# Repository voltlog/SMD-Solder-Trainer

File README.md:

# SMD-Solder-Trainer
This repository holds source file for the Voltlog SMD Solder Trainer

I designed this PCB to help people test their SMD soldering skills. It contains passives from 01005 up to 1206 as well as several chip packages. If you solder all resistors in a row and the LED correctly, by applying 5V to the bottom header you should get a light on the LED. Although not entirely necessary, if you order this board with ENIG gold finish it should help with soldering the smallest pads.

Here is a list of tools & supplies that I used in this project:
* 2x3W Gooseneck Microscope Light http://voltlog.com/y/2gxc9
* Trinocular Microscope http://voltlog.com/y/tcmpe
* Hayear 1080P Camera http://voltlog.com/y/uh7pv
* 10” 2K HDMI Monitor http://voltlog.com/y/nq7rv
* KSGER T12 Soldering Station http://voltlog.com/y/2tzg7
* PCB files Kicad/Gerber (in this repository)

More info about this project in [Voltlog #328](https://youtu.be/IcV3Eh1Z-N4).

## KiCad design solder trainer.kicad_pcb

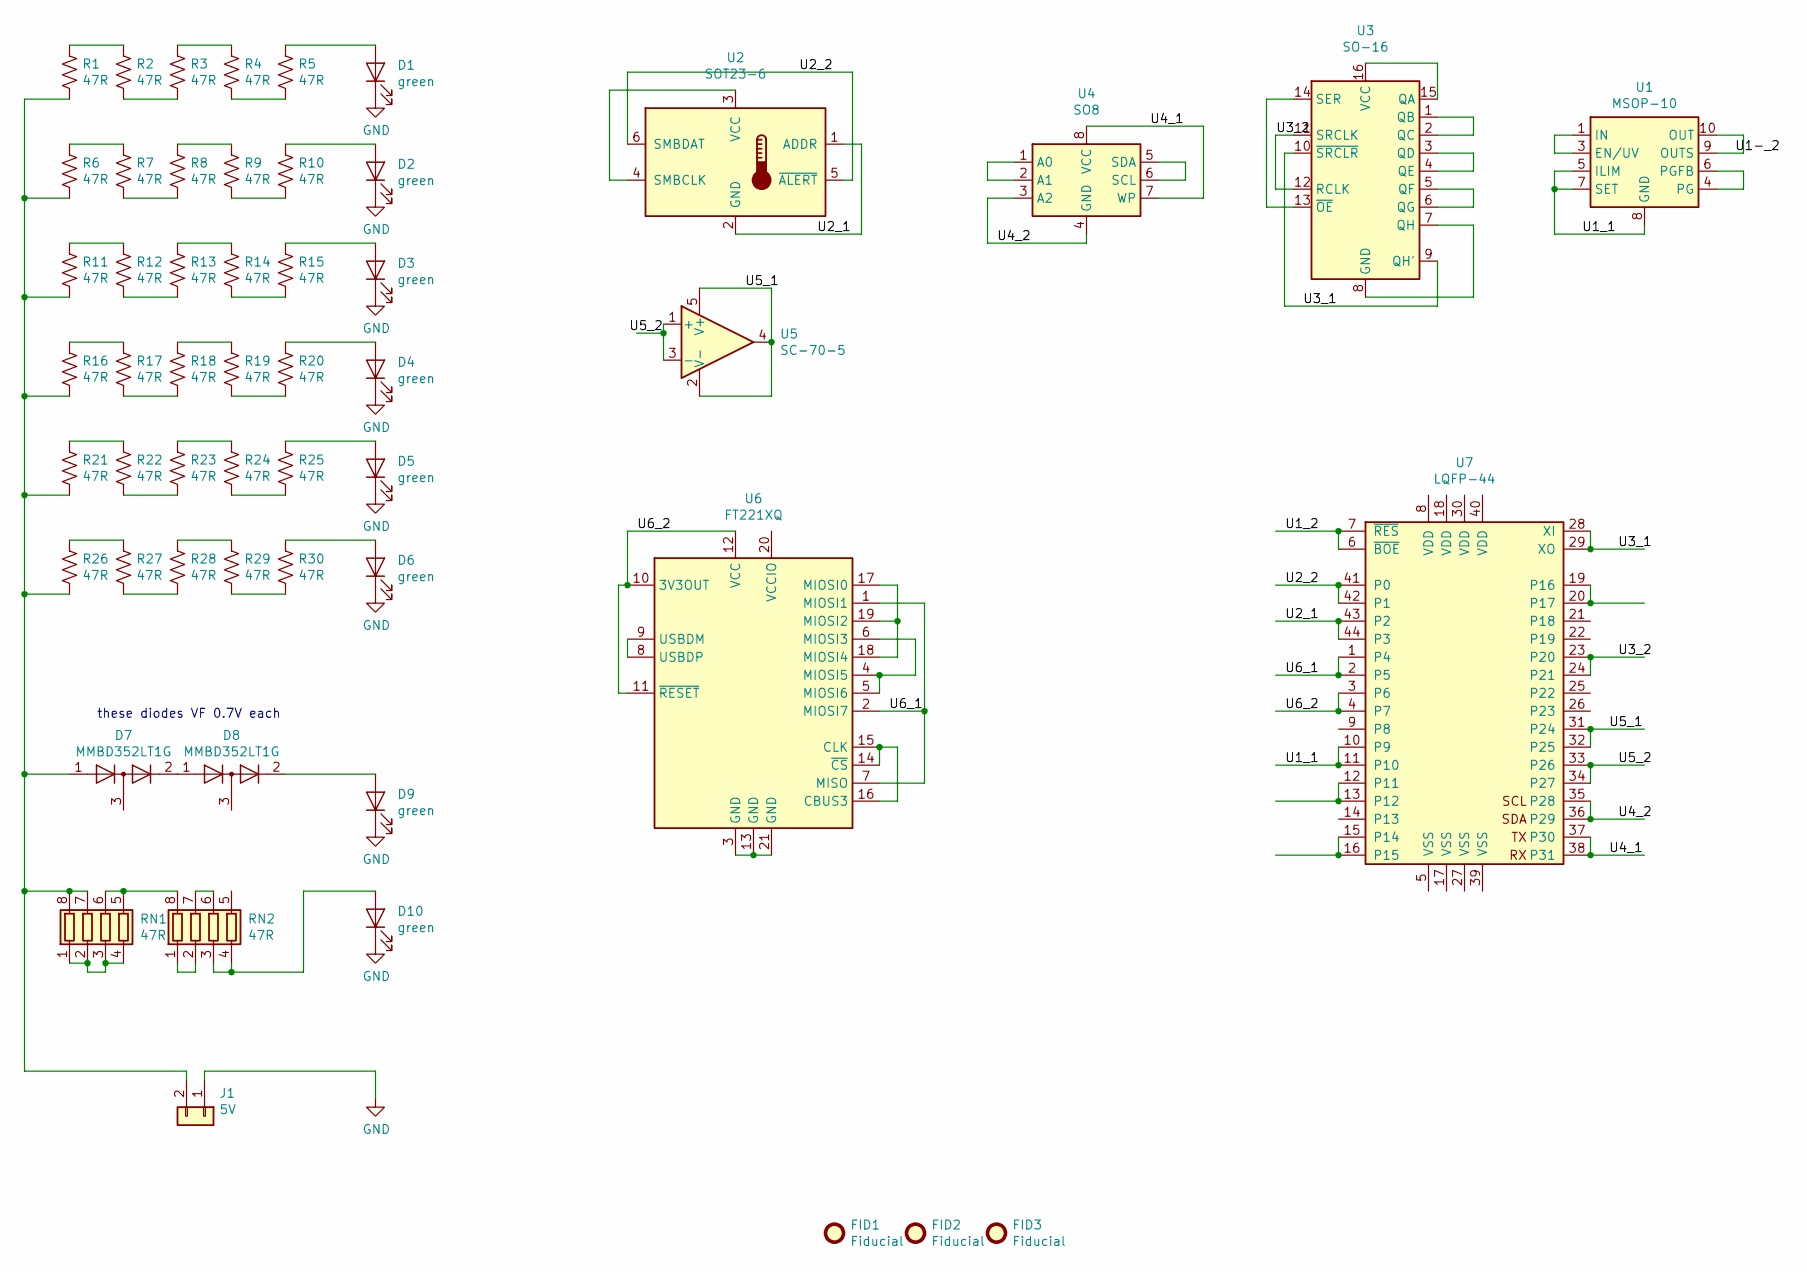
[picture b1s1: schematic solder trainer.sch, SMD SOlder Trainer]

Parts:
D1, D2, D3: green; LED_0402_1005Metric; LCSC C268302
D4, D9, D10: green; LED_0603_1608Metric_Pad1.05x0.95mm_HandSolder; LCSC C268302
D5: green; LED_0805_2012Metric_Pad1.15x1.40mm_HandSolder; LCSC C268302
D6: green; LED_1206_3216Metric_Pad1.42x1.75mm_HandSolder; LCSC C268302
D7, D8: MMBD352LT1G; SOT-23; LCSC C463549
FID1, FID2, FID3: Fiducial; Fiducial_0.5mm_Dia_1mm_Outer
J1: 5V; PinHeader_1x02_P2.54mm_Vertical
R1, R2, R3, R4, R5: 47R; R_01005_0402Metric
R6, R7, R8, R9, R10: 47R; R_0201_0603Metric
R11, R12, R13, R14, R15: 47R; R_0402_1005Metric
R16, R17, R18, R19, R20: 47R; R_0603_1608Metric_Pad1.05x0.95mm_HandSolder
R21, R22, R23, R24, R25: 47R; R_0805_2012Metric_Pad1.15x1.40mm_HandSolder
R26, R27, R28, R29, R30: 47R; R_1206_3216Metric_Pad1.42x1.75mm_HandSolder
RN1, RN2: 47R; R_Array_Convex_4x0603
U1: MSOP-10; MSOP-10-1EP_3x3mm_P0.5mm_EP1.68x1.88mm
U2: SOT23-6; SOT-23-6
U3: SO-16; SOIC-16_3.9x9.9mm_P1.27mm
U4: SO8; SOIC-8_3.9x4.9mm_P1.27mm
U5: SC-70-5; SOT-353_SC-70-5_Handsoldering
U6: FT221XQ; QFN-20-1EP_4x4mm_P0.5mm_EP2.5x2.5mm
U7: LQFP-44; LQFP-44_10x10mm_P0.8mm

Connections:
/U1-_2: U1.9 (OUTS), U1.10 (OUT)
/U1_1: U1.5 (ILIM), U1.7 (SET), U1.8 (GND), U1.11 (GND), U7.10 (P9), U7.11 (P10)
/U1_2: U7.6 (~BOE), U7.7 (~RES)
/U2_1: U2.1 (ADDR), U2.2 (GND), U7.43 (P2), U7.44 (P3)
/U2_2: U2.5 (~ALERT), U2.6 (SMBDAT), U7.41 (P0), U7.42 (P1)
/U3_1: U3.9 (QH'), U3.10 (~SRCLR), U7.28 (XI), U7.29 (XO)
/U3_2: U3.11 (SRCLK), U3.12 (RCLK), U7.23 (P20), U7.24 (P21)
/U4_1: U4.7 (WP), U4.8 (VCC), U7.37 (P30), U7.38 (P31)
/U4_2: U4.3 (A2), U4.4 (GND), U7.35 (P28), U7.36 (P29)
/U5_1: U5.2 (V-), U5.4, U5.5 (V+), U7.31 (P24), U7.32 (P25)
/U5_2: U5.1 (+), U5.3 (-), U7.33 (P26), U7.34 (P27)
/U6_1: U6.1 (MIOSI1), U6.2 (MIOSI7), U6.7 (MISO), U7.1 (P4), U7.2 (P5)
/U6_2: U6.10 (3V3OUT), U6.11 (~RESET), U6.12 (VCC), U7.3 (P6), U7.4 (P7)
GND: D1.1 (K), D2.1 (K), D3.1 (K), D4.1 (K), D5.1 (K), D6.1 (K), D9.1 (K), D10.1 (K), J1.1
unnamed: D1.2 (A), R5.1
unnamed: D2.2 (A), R10.1
unnamed: D3.2 (A), R15.1
unnamed: D4.2 (A), R20.1
unnamed: D5.2 (A), R25.1
unnamed: D6.2 (A), R30.1
unnamed: D7.1 (K), J1.2, R1.2, R6.2, R11.2, R16.2, R21.2, R26.2, RN1.7 (R2.2), RN1.8 (R1.2)
unnamed: D7.2 (A), D8.1 (K)
unnamed: D8.2 (A), D9.2 (A)
unnamed: D10.2 (A), RN2.3 (R3.1), RN2.4 (R4.1)
unnamed: R1.1, R2.1
unnamed: R2.2, R3.2
unnamed: R3.1, R4.1
unnamed: R4.2, R5.2
unnamed: R6.1, R7.1
unnamed: R7.2, R8.2
unnamed: R8.1, R9.1
unnamed: R9.2, R10.2
unnamed: R11.1, R12.1
unnamed: R12.2, R13.2
unnamed: R13.1, R14.1
unnamed: R14.2, R15.2
unnamed: R16.1, R17.1
unnamed: R17.2, R18.2
unnamed: R18.1, R19.1
unnamed: R19.2, R20.2
unnamed: R21.1, R22.1
unnamed: R22.2, R23.2
unnamed: R23.1, R24.1
unnamed: R24.2, R25.2
unnamed: R26.1, R27.1
unnamed: R27.2, R28.2
unnamed: R28.1, R29.1
unnamed: R29.2, R30.2
unnamed: RN1.1 (R1.1), RN1.2 (R2.1), RN1.3 (R3.1), RN1.4 (R4.1)
unnamed: RN1.5 (R4.2), RN1.6 (R3.2), RN2.8 (R1.2)
unnamed: RN2.1 (R1.1), RN2.2 (R2.1)
unnamed: RN2.6 (R3.2), RN2.7 (R2.2)
unnamed: U1.1 (IN), U1.2 (IN), U1.3 (EN/UV)
unnamed: U1.4 (PG), U1.6 (PGFB)
unnamed: U2.3 (VCC), U2.4 (SMBCLK)
unnamed: U3.1 (QB), U3.2 (QC)
unnamed: U3.3 (QD), U3.4 (QE)
unnamed: U3.5 (QF), U3.6 (QG)
unnamed: U3.7 (QH), U3.8 (GND)
unnamed: U3.13 (~OE), U3.14 (SER)
unnamed: U3.15 (QA), U3.16 (VCC)
unnamed: U4.1 (A0), U4.2 (A1)
unnamed: U4.5 (SDA), U4.6 (SCL)
unnamed: U6.4 (MIOSI5), U6.5 (MIOSI6), U6.6 (MIOSI3)
unnamed: U6.8 (USBDP), U6.9 (USBDM)
unnamed: U6.3 (GND), U6.13 (GND), U6.21 (GND)
unnamed: U6.14 (~CS), U6.15 (CLK), U6.16 (CBUS3)
unnamed: U6.17 (MIOSI0), U6.18 (MIOSI4), U6.19 (MIOSI2)
unnamed: U7.12 (P11), U7.13 (P12)
unnamed: U7.15 (P14), U7.16 (P15)
unnamed: U7.19 (P16), U7.20 (P17)

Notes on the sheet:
these diodes VF 0.7V each

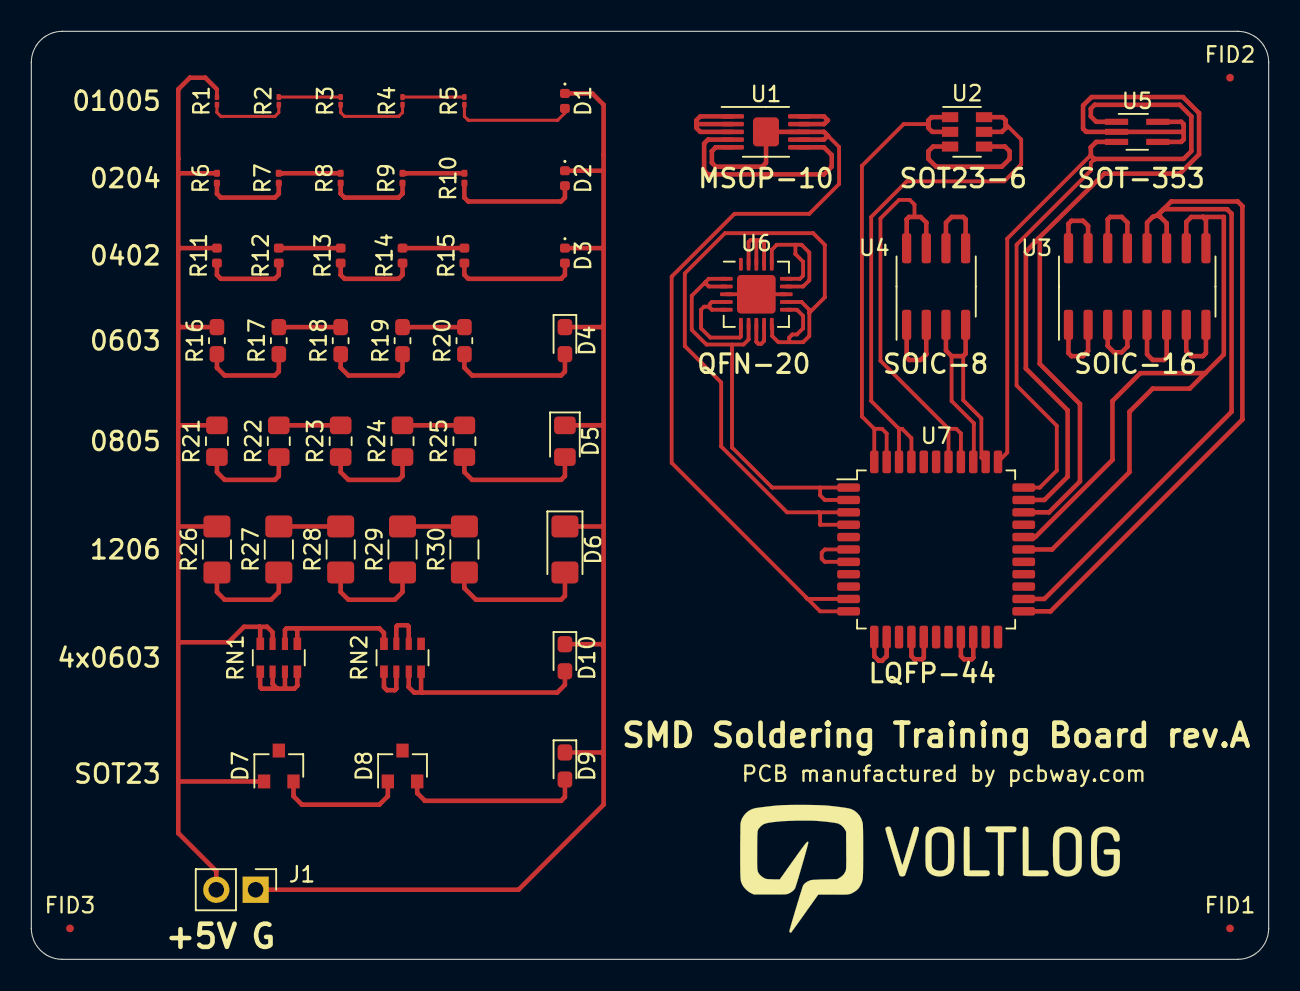
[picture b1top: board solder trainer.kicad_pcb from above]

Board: 2 copper layers, 80.0 x 60.0 mm, 53 parts (0 on the bottom side), 71 nets.

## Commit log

2020-09-04 Initial commit of files
